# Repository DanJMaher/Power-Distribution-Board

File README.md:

Updated 3/29/21 - Dan Maher

C++/Arduino code for Kent State's Advanced Telerobotic's Lab's WRS robot power distribution system. The system distributes switched 24V and 12V power throughout the robot, monitors voltage, and communicates over USB and Bluetooth via JSON commands and messages. The system can also be controlled locally via an onboard OLED display and menu navigation buttons. 

The included serial_comm.py program is for testing communication between a PC and the Arduino. The system can also be tested via a Bluetooth terminal app for android or IOS.

Basic use:
1) Plug in an Arduino, send the code. 
2) run serial_comm.py (for basic communication) or power_monitor_pub.py for ROS integration on the 'power' topic.

When it boots, the Arduino tries to send a JSON message via serial:
{"request":"time"}

The python program responds via serial with the current time since midnight in seconds:
{"time": 70602, "alive": true}

Afterwards, the Arduino sends a status message via serial on the interval programmed in sendInterval in setup.cpp. The python program responds with {"alive": true} so that the Arduino knows that that communication path is good. The Arduino does not send another message until it receives a response.

The serial_comm.py program is just for troubleshooting, and copies the incoming/outgoing serial messages to the console so the user can see what's being sent/received.
---------------------------------------------------------------------------
REMOTE JSON COMMANDS
---------------------------------------------------------------------------
{"relay":[bool, bool]}		-		Sets individual relays to on/off

{"time":unsigned long}		-		Sync system time with long (in seconds)

{"shutdown":"now"}		-		Shuts down the system with code "remote"

---------------------------------------------------------------------------
INCOMING JSON MESSAGES
---------------------------------------------------------------------------

{"msg":int}			-		Message number

{"time":unsigned long}		-		Current timestamp

{"voltage:[float,float]}	-		Current voltages (11.1, 22.2)

{"relay":[bool,bool]}		-		Current relay status (11.1, 22.2)

{"comm status"[bool, bool]}	-		Current comm status path 1/2 (false is communication failure)

{"SHUTDOWN":string} 		-		System is shutting down for reason:
							"auto" - low voltage
							"remote" - remote serial command
							"button" - power button was pushed

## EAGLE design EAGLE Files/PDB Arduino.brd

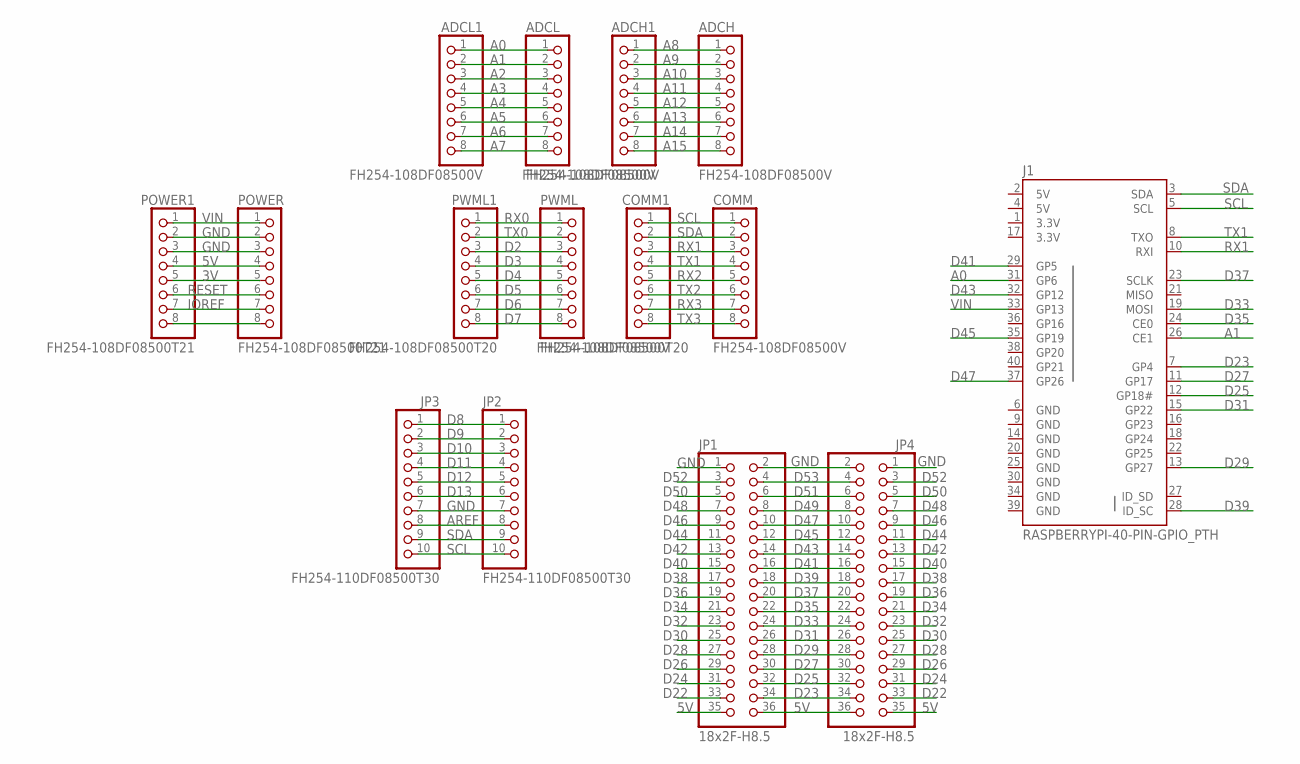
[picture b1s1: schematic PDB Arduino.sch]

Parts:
ADCH, ADCH1: FH254-108DF08500V; CONNETTORI_1X08
ADCL, ADCL1: FH254-108DF08500V; CONNETTORI_1X08
COMM, COMM1: FH254-108DF08500V; CONNETTORI_1X08
J1: RASPBERRYPI-40-PIN-GPIO_PTH; 2X20_SHROUDED
JP1, JP4: 18x2F-H8.5; CONNETTORI_2X18
JP2, JP3: FH254-110DF08500T30; CONNETTORI_1X10
POWER, POWER1: FH254-108DF08500T21; CONNETTORI_1X08
PWML, PWML1: FH254-108DF08500T20; CONNETTORI_1X08

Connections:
3.3V: J1.1 (3.3V), J1.17 (3.3V)
3V: POWER.5, POWER1.5
5V: J1.2 (5V), J1.4 (5V), JP1.35, JP1.36, JP4.35, JP4.36, POWER.4, POWER1.4
A0: ADCL.1, ADCL1.1, J1.31 (GP6)
A1: ADCL.2, ADCL1.2, J1.26 (CE1)
A2: ADCL.3, ADCL1.3
A3: ADCL.4, ADCL1.4
A4: ADCL.5, ADCL1.5
A5: ADCL.6, ADCL1.6
A6: ADCL.7, ADCL1.7
A7: ADCL.8, ADCL1.8
A8: ADCH.1, ADCH1.1
A9: ADCH.2, ADCH1.2
A10: ADCH.3, ADCH1.3
A11: ADCH.4, ADCH1.4
A12: ADCH.5, ADCH1.5
A13: ADCH.6, ADCH1.6
A14: ADCH.7, ADCH1.7
A15: ADCH.8, ADCH1.8
AREF: JP2.8, JP3.8
D2: PWML.3, PWML1.3
D3: PWML.4, PWML1.4
D4: PWML.5, PWML1.5
D5: PWML.6, PWML1.6
D6: PWML.7, PWML1.7
D7: PWML.8, PWML1.8
D8: JP2.1, JP3.1
D9: JP2.2, JP3.2
D10: JP2.3, JP3.3
D11: JP2.4, JP3.4
D12: JP2.5, JP3.5
D13: JP2.6, JP3.6
D22: JP1.33, JP4.33
D23: J1.7 (GP4), JP1.34, JP4.34
D24: JP1.31, JP4.31
D25: J1.12 (GP18#), JP1.32, JP4.32
D26: JP1.29, JP4.29
D27: J1.11 (GP17), JP1.30, JP4.30
D28: JP1.27, JP4.27
D29: J1.13 (GP27), JP1.28, JP4.28
D30: JP1.25, JP4.25
D31: J1.15 (GP22), JP1.26, JP4.26
D32: JP1.23, JP4.23
D33: J1.19 (MOSI), JP1.24, JP4.24
D34: JP1.21, JP4.21
D35: J1.24 (CE0), JP1.22, JP4.22
D36: JP1.19, JP4.19
D37: J1.23 (SCLK), JP1.20, JP4.20
D38: JP1.17, JP4.17
D39: J1.28 (ID_SC), JP1.18, JP4.18
D40: JP1.15, JP4.15
D41: J1.29 (GP5), JP1.16, JP4.16
D42: JP1.13, JP4.13
D43: J1.32 (GP12), JP1.14, JP4.14
D44: JP1.11, JP4.11
D45: J1.35 (GP19), JP1.12, JP4.12
D46: JP1.9, JP4.9
D47: J1.37 (GP26), JP1.10, JP4.10
D48: JP1.7, JP4.7
D49: JP1.8, JP4.8
D50: JP1.5, JP4.5
D51: JP1.6, JP4.6
D52: JP1.3, JP4.3
D53: JP1.4, JP4.4
GND: J1.6 (GND), J1.9 (GND), J1.14 (GND), J1.20 (GND), J1.25 (GND), J1.30 (GND), J1.34 (GND), J1.39 (GND), JP1.1, JP1.2, JP2.7, JP3.7, JP4.1, JP4.2, POWER.2, POWER.3, POWER1.2, POWER1.3
IOREF: POWER.7, POWER1.7
unnamed: POWER.8, POWER1.8
RESET: POWER.6, POWER1.6
RX0: PWML.1, PWML1.1
RX1: COMM.3, COMM1.3, J1.10 (RXI)
RX2: COMM.5, COMM1.5
RX3: COMM.7, COMM1.7
SCL: COMM.1, COMM1.1, J1.5 (SCL), JP2.10, JP3.10
SDA: COMM.2, COMM1.2, J1.3 (SDA), JP2.9, JP3.9
TX0: PWML.2, PWML1.2
TX1: COMM.4, COMM1.4, J1.8 (TXO)
TX2: COMM.6, COMM1.6
TX3: COMM.8, COMM1.8
VIN: J1.33 (GP13), POWER.1, POWER1.1

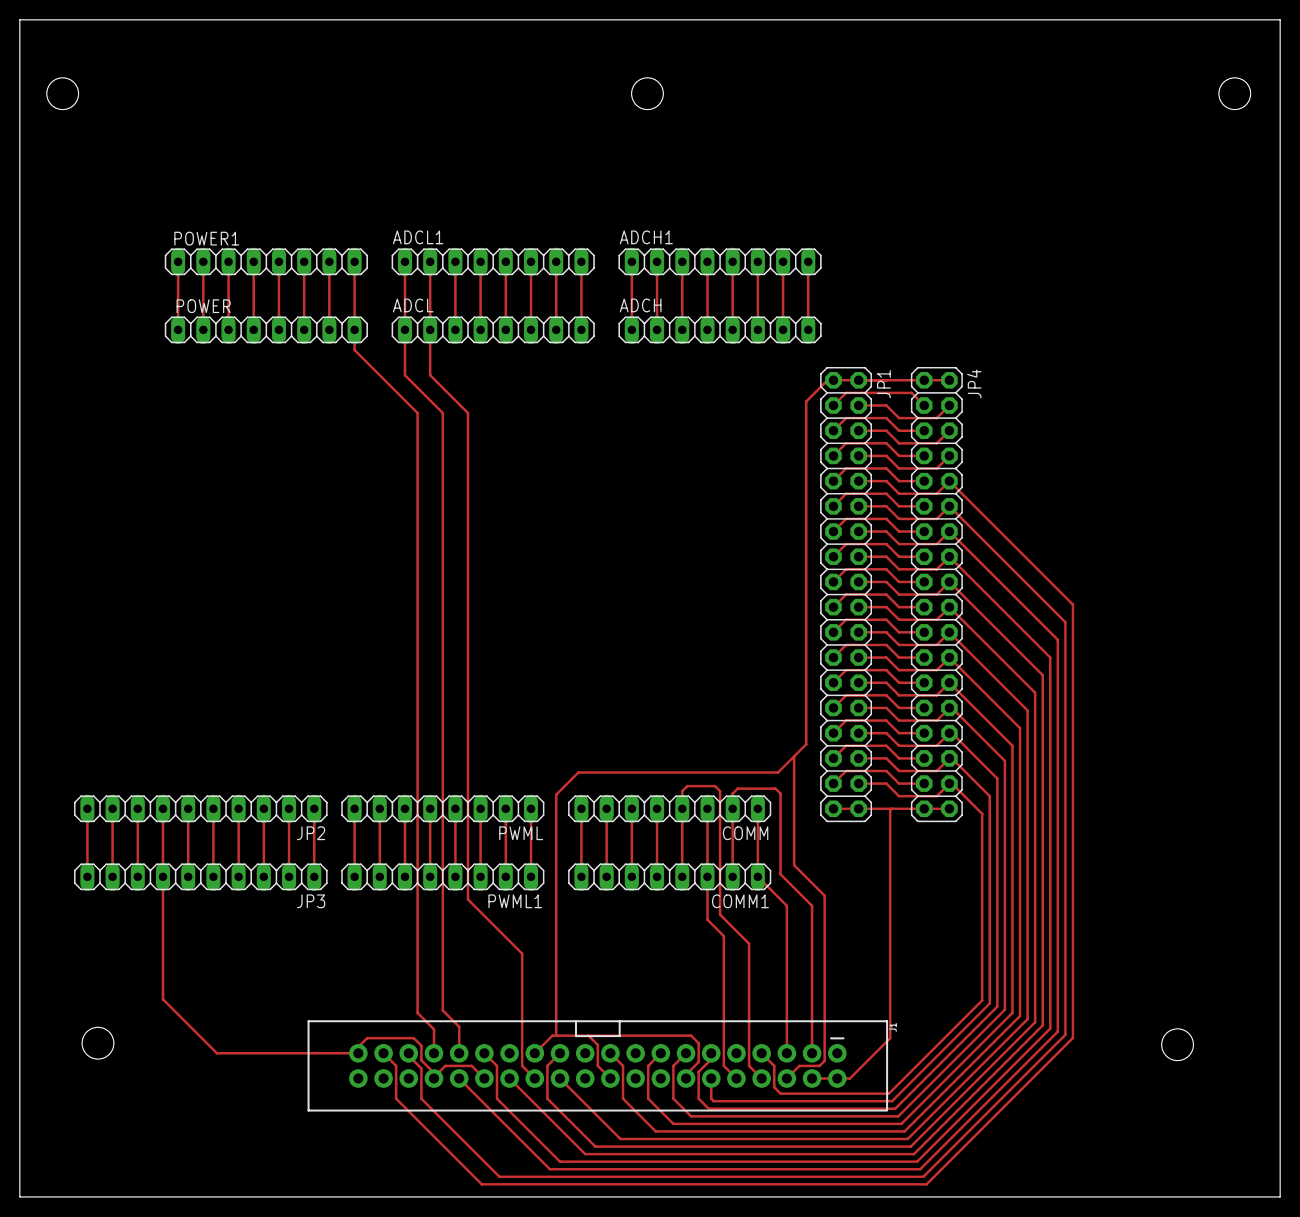
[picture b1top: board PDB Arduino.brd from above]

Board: 2 copper layers, 127.0 x 118.6 mm, 15 parts (0 on the bottom side), 79 nets.

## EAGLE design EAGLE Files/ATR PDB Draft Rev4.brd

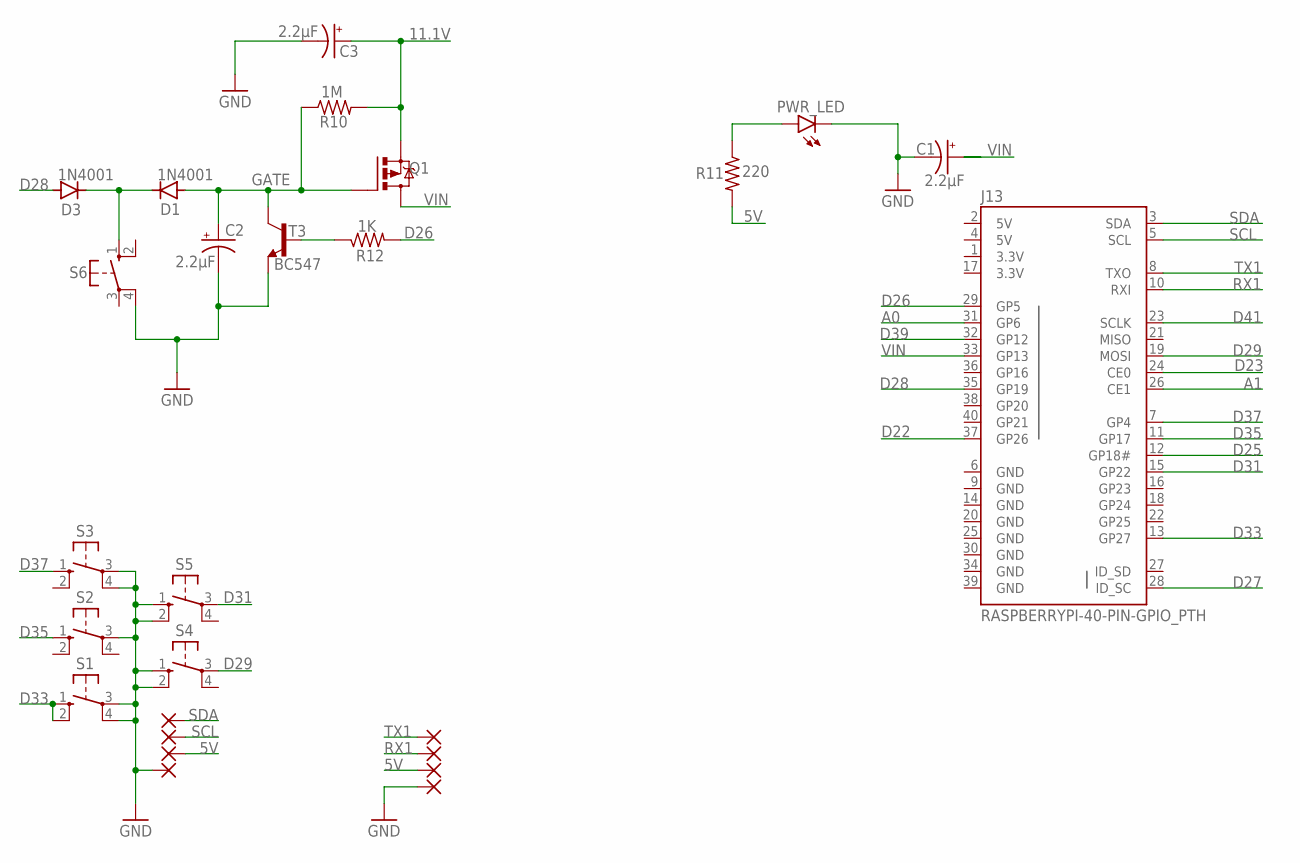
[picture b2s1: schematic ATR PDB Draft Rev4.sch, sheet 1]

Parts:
C1, C2, C3: 2.2µF; TT2D5
D1, D3: 1N4004; DO41-10
J13: RASPBERRYPI-40-PIN-GPIO_PTH; 2X20_SHROUDED
PAD1, PAD2, PAD3, PAD4, PAD5, PAD6, PAD7, PAD8: 1,6/0,8
PWR_LED: LED3MM
Q1: IRF9530; TO220BV
R10: 1M; 0207/10
R11: 220; 0204/7
R12: 1K; 0204/7
S1, S2, S3, S4, S5, S6: 10-XX; B3F-10XX
T3: BC547; TO92

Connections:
3.3V: J13.1 (3.3V), J13.17 (3.3V)
5V: J13.2 (5V), J13.4 (5V), PAD1.1, PAD7.1, R11.2
11.1V: C3.+, Q1.S, R10.2; also elsewhere on the board
A0: J13.31 (GP6); also elsewhere on the board
A1: J13.26 (CE1); also elsewhere on the board
D22: J13.37 (GP26); also elsewhere on the board
D23: J13.24 (CE0); also elsewhere on the board
D25: J13.12 (GP18#); also elsewhere on the board
D26: J13.29 (GP5), R12.2
D27: J13.28 (ID_SC); also elsewhere on the board
D28: D3.A, J13.35 (GP19)
D29: J13.19 (MOSI), S4.3
D31: J13.15 (GP22), S5.3
D33: J13.13 (GP27), S1.1 (S), S1.2 (S1)
D35: J13.11 (GP17), S2.1 (S)
D37: J13.7 (GP4), S3.1 (S)
D39: J13.32 (GP12); also elsewhere on the board
D41: J13.23 (SCLK); also elsewhere on the board
GATE: C2.+, D1.A, Q1.G, R10.1, T3.3 (C)
GND: C1.-, C2.-, C3.-, J13.6 (GND), J13.9 (GND), J13.14 (GND), J13.20 (GND), J13.25 (GND), J13.30 (GND), J13.34 (GND), J13.39 (GND), PAD3.1, PAD8.1, PWR_LED.K (C), S1.3, S1.4 (P1), S2.3, S3.3, S3.4 (P1), S4.1 (S), S4.2 (S1), S5.1 (S), S5.2 (S1), S6.4 (P1), T3.1 (E); also elsewhere on the board
unnamed: PWR_LED.A, R11.1
unnamed: D1.C, D3.C, S6.1 (S)
RX1: J13.10 (RXI), PAD2.1
SCL: J13.5 (SCL), PAD6.1
SDA: J13.3 (SDA), PAD5.1
T3-B: R12.1, T3.2 (B)
TX1: J13.8 (TXO), PAD4.1
VIN: C1.+, J13.33 (GP13), Q1.D

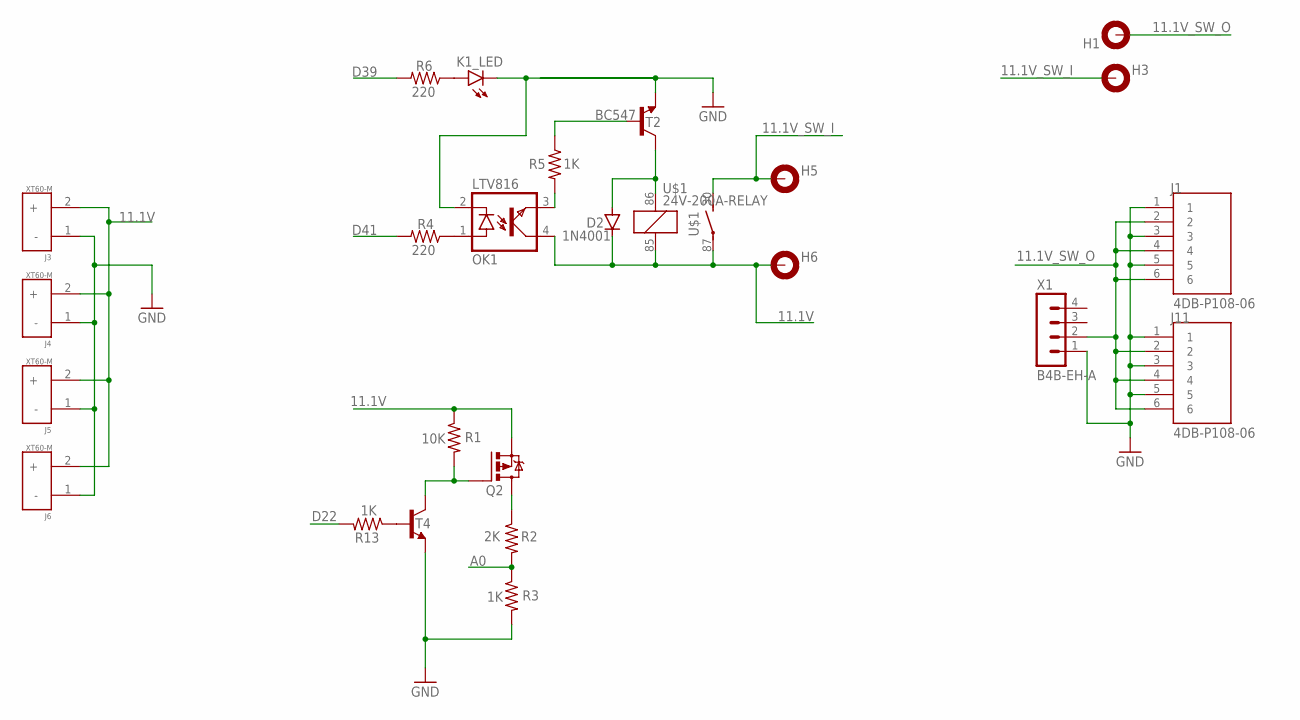
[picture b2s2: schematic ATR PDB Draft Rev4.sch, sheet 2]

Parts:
D2: 1N4004; DO41-10
H1, H3, H5, H6: MOUNT-PAD-ROUND3.0; 3,0-PAD
J1, J11: 4DB-P108-06; TE_2-1437667-9
J3, J4, J5, J6: XT60-M; AMASS_XT60-M
K1_LED: LED3MM
OK1: LTV816; DIL04
Q2: IRF9530; TO220BV
R1: 10K; 0204/7
R2: 2K; 0204/7
R3, R5, R13: 1K; 0204/7
R4, R6: 220; 0204/7
T2, T4: BC547; TO92
U$1: 24V-200A-RELAY
X1: B4B-EH-A

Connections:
11.1V: D2.C, H6.B3,0, J3.2 (+), J4.2 (+), J5.2 (+), J6.2 (+), OK1.4 (COL), Q2.S, R1.1, U$1.85, U$1.87; also elsewhere on the board
11.1V_SW_I: H3.B3,0, H5.B3,0, U$1.30
11.1V_SW_O: H1.B3,0, J1.2, J1.4, J1.6, J11.2, J11.4, J11.6, X1.2
A0: R2.2, R3.1; also elsewhere on the board
D22: R13.2; also elsewhere on the board
D39: R6.2; also elsewhere on the board
D41: R4.2; also elsewhere on the board
DRAIN1: Q2.D, R2.1
GATE1: Q2.G, R1.2, T4.3 (C)
GND: J1.1, J1.3, J1.5, J3.1 (-), J4.1 (-), J5.1 (-), J6.1 (-), J11.1, J11.3, J11.5, K1_LED.K (C), OK1.2 (C), R3.2, T2.1 (E), T4.1 (E), X1.1; also elsewhere on the board
unnamed: OK1.1 (A), R4.1
unnamed: K1_LED.A, R6.1
unnamed: R13.1, T4.2 (B)
unnamed: OK1.3 (EMIT), R5.2
unnamed: R5.1, T2.2 (B)
unnamed: D2.A, T2.3 (C), U$1.86

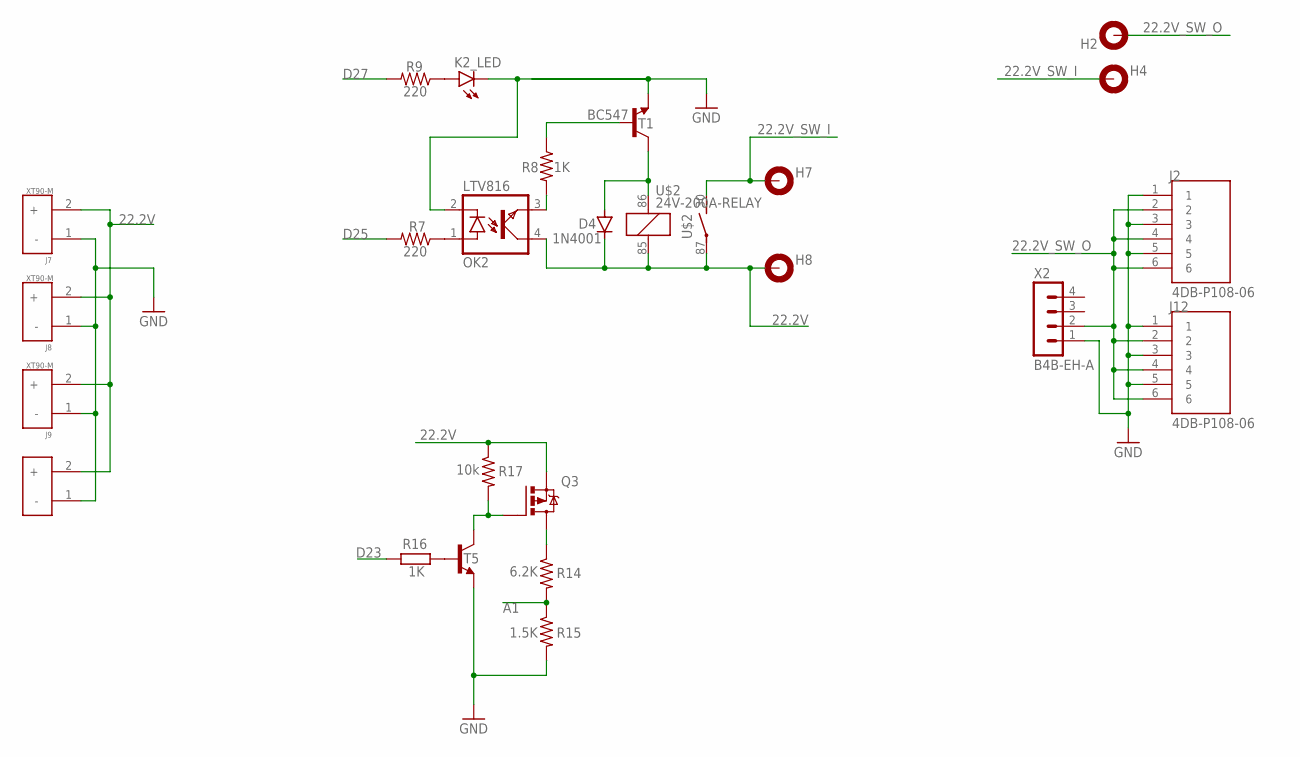
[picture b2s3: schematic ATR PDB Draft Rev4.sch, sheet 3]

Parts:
D4: 1N4004; DO41-10
H2, H4, H7, H8: MOUNT-PAD-ROUND3.0; 3,0-PAD
J2, J12: 4DB-P108-06; TE_2-1437667-9
J7, J8, J9, J10: XT90-M; AMASS_XT90-M
K2_LED: LED3MM
OK2: LTV816; DIL04
Q3: IRF9530; TO220BV
R7, R9: 220; 0204/7
R8, R16: 1K; 0204/7
R14: 6.2K; 0204/7
R15: 1.5K; 0207/10
R17: 10k; 0204/7
T1, T5: BC547; TO92
U$2: 24V-200A-RELAY
X2: B4B-EH-A

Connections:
22.2V: D4.C, H8.B3,0, J7.2 (+), J8.2 (+), J9.2 (+), J10.2 (+), OK2.4 (COL), Q3.S, R17.1, U$2.85, U$2.87
22.2V_SW_I: H4.B3,0, H7.B3,0, U$2.30
22.2V_SW_O: H2.B3,0, J2.2, J2.4, J2.6, J12.2, J12.4, J12.6, X2.2
A1: R14.2, R15.1; also elsewhere on the board
D23: R16.2; also elsewhere on the board
D25: R7.2; also elsewhere on the board
D27: R9.2; also elsewhere on the board
DRAIN2: Q3.D, R14.1
GATE2: Q3.G, R17.2, T5.3 (C)
GND: J2.1, J2.3, J2.5, J7.1 (-), J8.1 (-), J9.1 (-), J10.1 (-), J12.1, J12.3, J12.5, K2_LED.K (C), OK2.2 (C), R15.2, T1.1 (E), T5.1 (E), X2.1; also elsewhere on the board
unnamed: OK2.3 (EMIT), R8.2
unnamed: R8.1, T1.2 (B)
unnamed: D4.A, T1.3 (C), U$2.86
unnamed: OK2.1 (A), R7.1
unnamed: K2_LED.A, R9.1
unnamed: R16.1, T5.2 (B)

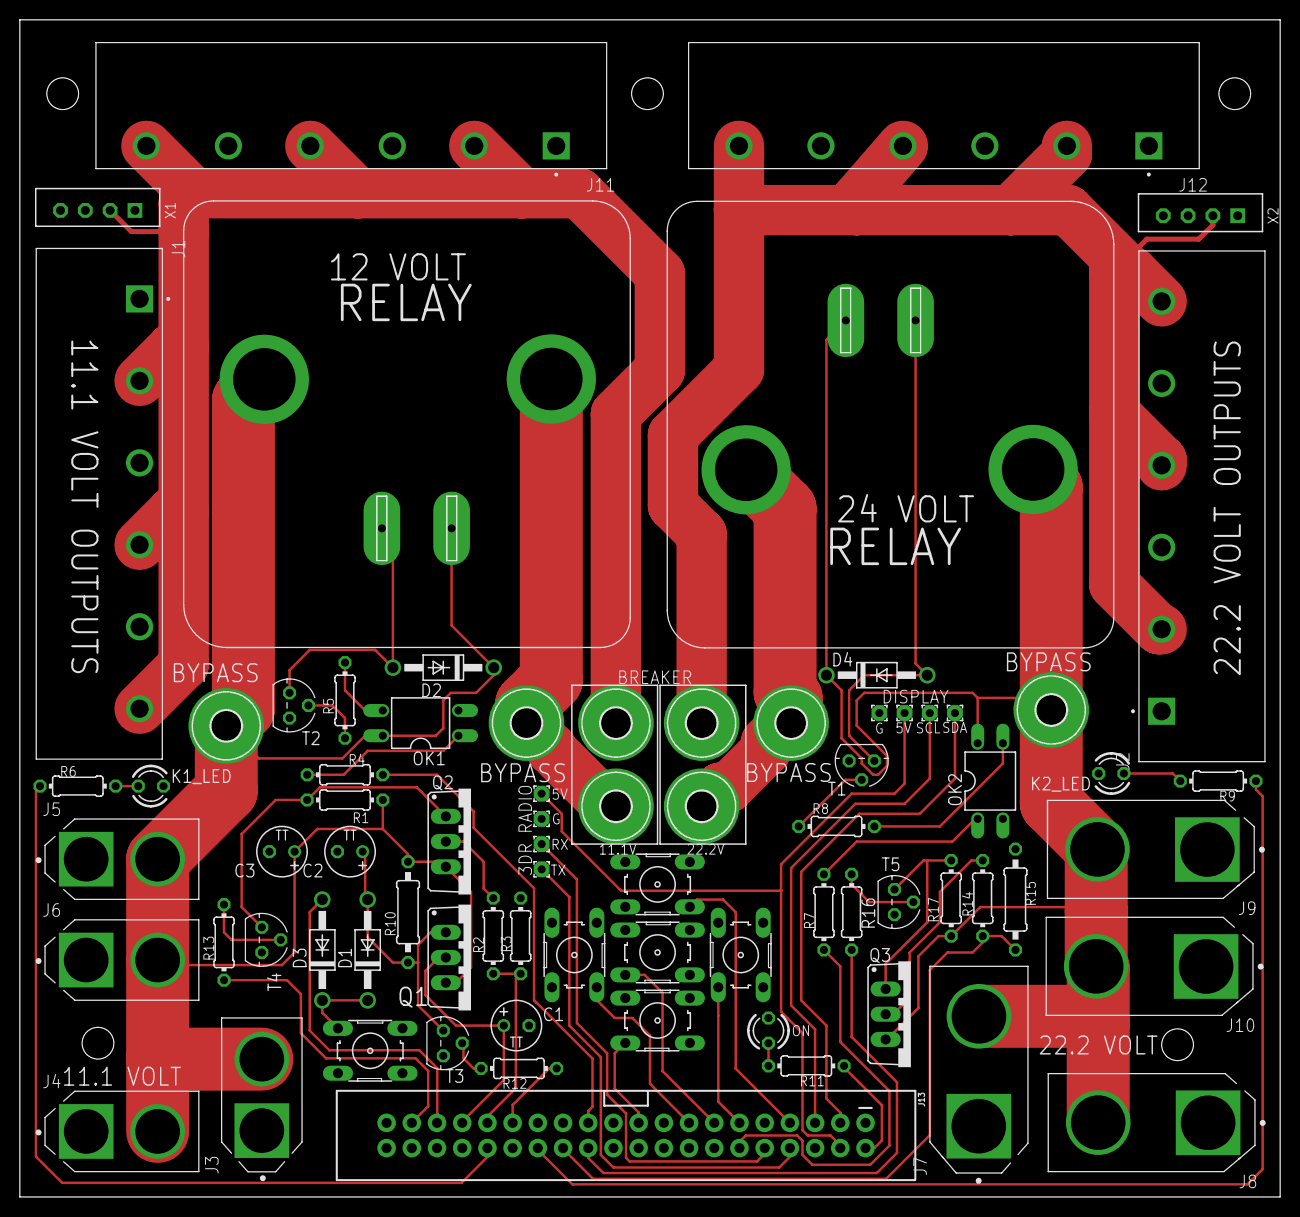
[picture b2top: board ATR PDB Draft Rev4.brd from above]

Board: 2 copper layers, 127.0 x 118.6 mm, 76 parts (0 on the bottom side), 49 nets.

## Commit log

2021-03-19 Adding main PDB project for ATR lab
2021-03-20 Test commit
2021-03-26 Added basic incoming message handling. "Alive" json messages on a steady interval.
2021-03-26 Restructured code to utilize classes
2021-03-26 Removed old directory
2021-03-26 Modified comm functions to handle stream ptrs
2021-03-26 Added Supervision::supervise() function to monitor system
2021-03-27 Cleaned up code
2021-03-27 Added data class instead of storing data in json doc
2021-03-27 Added time sync on boot and timestamp in seconds since midnight
2021-03-28 Added summary comments in all files
2021-03-29 Added readme
2021-03-30 Added remote command handling
2021-03-30 Added basic serial1 communication
2021-04-01 Added wireless comm and changed Comm class from static to instanced
2021-04-02 added screen class and some basic screen functionality. Can now display voltage and relay status actively
2021-04-06 added basic menu w/scroll. No functionality yet
2021-04-06 Single page menu working with 11.1v relay on/off
2021-04-26 Added basic ROS publisher topic and fixed speed bugs due to Serial.readString. Made a custom algorithm instead
2021-04-26 Added EAGLE .brd and .sch files
2021-10-02 Rename Readme.txt to README.md

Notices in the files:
parts and their libraries:
SparkFun-Connectors: Licensing: Creative Commons ShareAlike 4.0 International - https://creativecommons.org/licenses/by-sa/4.0
